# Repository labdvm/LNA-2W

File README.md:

# LNA-2W
High Linearity Amplifier 2W
Working frequency 50MHz - 1.5GHz.
450-800MHz
V1.2
Z32IT

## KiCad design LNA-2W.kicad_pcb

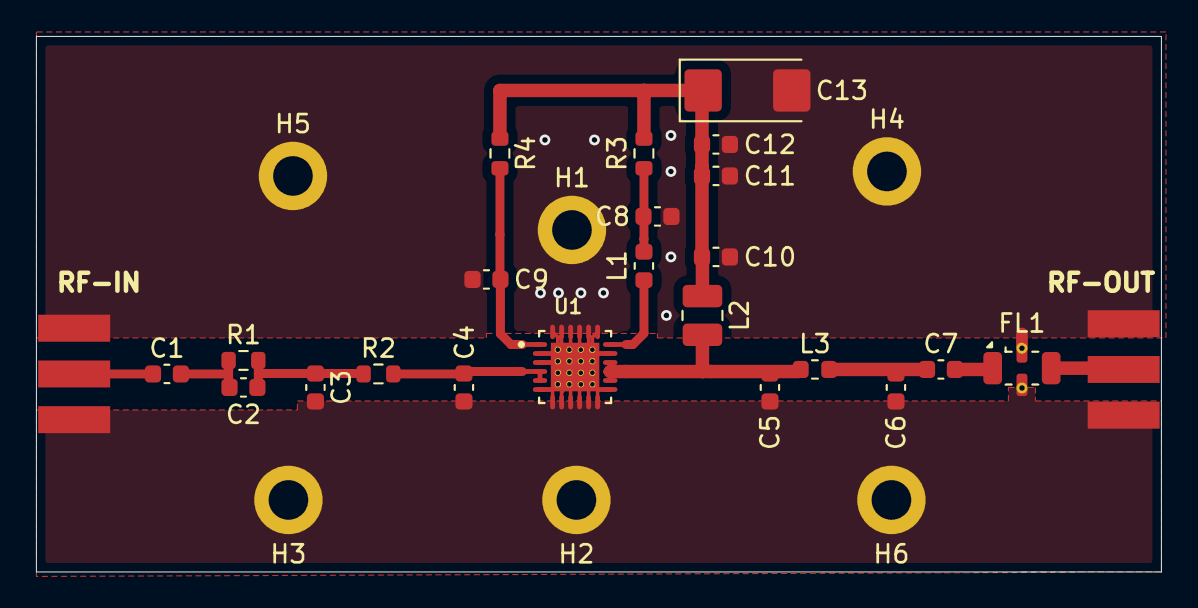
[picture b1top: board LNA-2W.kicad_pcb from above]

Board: 2 copper layers, 62.5 x 29.8 mm, 30 parts (0 on the bottom side), 13 nets.

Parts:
C1, C2, C8, C9, C11: 100p; C_0603_1608Metric
C3, C5: 8p2; C_0603_1608Metric
C4: 15p; C_0603_1608Metric
C6: 6p8; C_0603_1608Metric
C7: 22p; C_0603_1608Metric
C10, C12: 1n; C_0603_1608Metric
C13: 10u; CP_EIA-6032-28_Kemet-C
FL1: LFCN-490; Filter_Mini-Circuits_FV1206
H1, H2, H3, H4, H5, H6: MountingHole; MountingHole_2.2mm_M2_DIN965_Pad
J1: SMA_RF IN; SMA_Edge_6.3mm
J2: SMA_RF OUT; SMA_Edge_6.3mm
L1: 68n; L_0603_1608Metric
L2: 18n; L_1008_2520Metric
L3: 4n7; L_0603_1608Metric
R1: 51R; R_0603_1608Metric
R2: 4R3; R_0603_1608Metric
R3, R4: 280R; R_0603_1608Metric
U1: TQP7M9106; QFN50P400X400X90-25N

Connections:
+5V: C10.1, C11.1, C12.1, C13.1, L2.1, R3.1, R4.1
GND: C3.2, C4.2, C5.2, C6.1, C8.1, C9.1, C10.2, C11.2, C12.2, C13.2, FL1.2 (GND), FL1.4 (GND), H1.1, H2.1, H3.1, H4.1, H5.1, H6.1, J1.2 (Ext), J2.2 (Ext), U1.2 (GND/NC), U1.3 (GND/NC), U1.6 (GND/NC), U1.7 (GND/NC), U1.8 (GND/NC), U1.9 (GND/NC), U1.10 (GND/NC), U1.11 (GND/NC), U1.12 (GND/NC), U1.13 (GND/NC), U1.17 (GND/NC), U1.19 (GND/NC), U1.20 (GND/NC), U1.21 (GND/NC), U1.22 (GND/NC), U1.23 (GND/NC), U1.24 (GND/NC), U1.25 (RF/DC_GND), U1.26 (RF/DC_GND), U1.27, U1.28, U1.29, U1.30, U1.31, U1.32, U1.33, U1.34, U1.35, U1.36, U1.37, U1.38, U1.39, U1.40, U1.41, U1.42
unnamed: C1.2, C2.1, R1.1
unnamed: C2.2, C3.1, R1.2, R2.1
unnamed: C4.1, R2.2, U1.4 (RF_IN), U1.5 (RF_IN)
unnamed: C5.1, L2.2, L3.1, U1.14 (RF_OUT/VCC), U1.15 (RF_OUT/VCC), U1.16 (RF_OUT/VCC)
unnamed: C6.2, C7.1, L3.2
unnamed: C8.2, L1.1, R3.2
unnamed: C7.2, FL1.1 (IN)
unnamed: FL1.3 (OUT), J2.1 (In)
unnamed: C1.1, J1.1 (In)
unnamed: L1.2, U1.18 (I_REF)
unnamed: C9.2, R4.2, U1.1 (VBIAS)
